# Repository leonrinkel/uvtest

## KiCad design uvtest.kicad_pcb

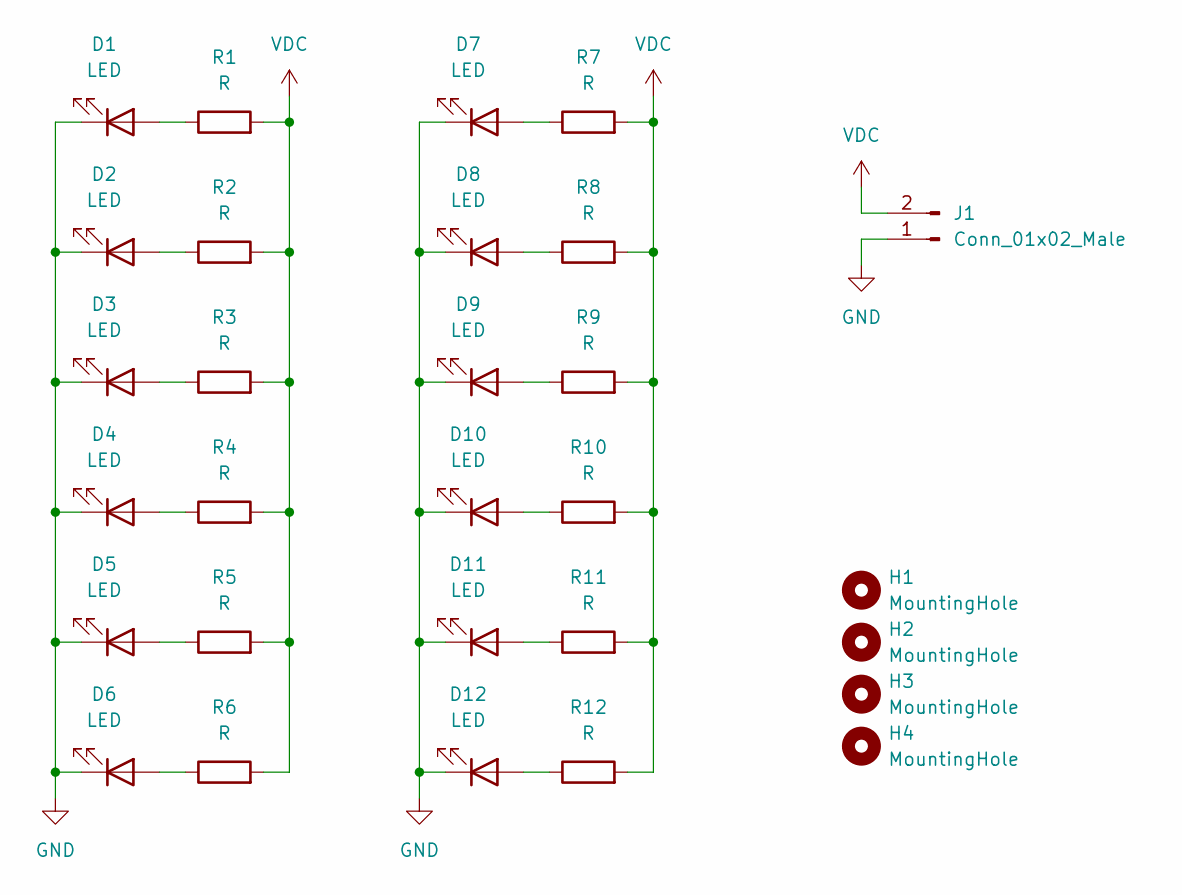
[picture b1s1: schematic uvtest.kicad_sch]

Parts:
D1: LED
D2, D3, D4, D5, D6, D7, D8, D9, D10, D11, D12: LED; LED_D5.0mm_Clear
H1: MountingHole
H2, H3, H4: MountingHole; MountingHole_2.7mm_M2.5
J1: Conn_01x02_Male
R1: R
R2, R3, R4, R5, R6, R7, R8, R9, R10, R11, R12: R; R_Axial_DIN0207_L6.3mm_D2.5mm_P10.16mm_Horizontal

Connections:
GND: D1.1 (K), D2.1 (K), D3.1 (K), D4.1 (K), D5.1 (K), D6.1 (K), D7.1 (K), D8.1 (K), D9.1 (K), D10.1 (K), D11.1 (K), D12.1 (K), J1.1
unnamed: D1.2 (A), R1.1
unnamed: D2.2 (A), R2.1
unnamed: D3.2 (A), R3.1
unnamed: D4.2 (A), R4.1
unnamed: D5.2 (A), R5.1
unnamed: D6.2 (A), R6.1
unnamed: D7.2 (A), R7.1
unnamed: D8.2 (A), R8.1
unnamed: D9.2 (A), R9.1
unnamed: D10.2 (A), R10.1
unnamed: D11.2 (A), R11.1
unnamed: D12.2 (A), R12.1
VDC: J1.2, R1.2, R2.2, R3.2, R4.2, R5.2, R6.2, R7.2, R8.2, R9.2, R10.2, R11.2, R12.2

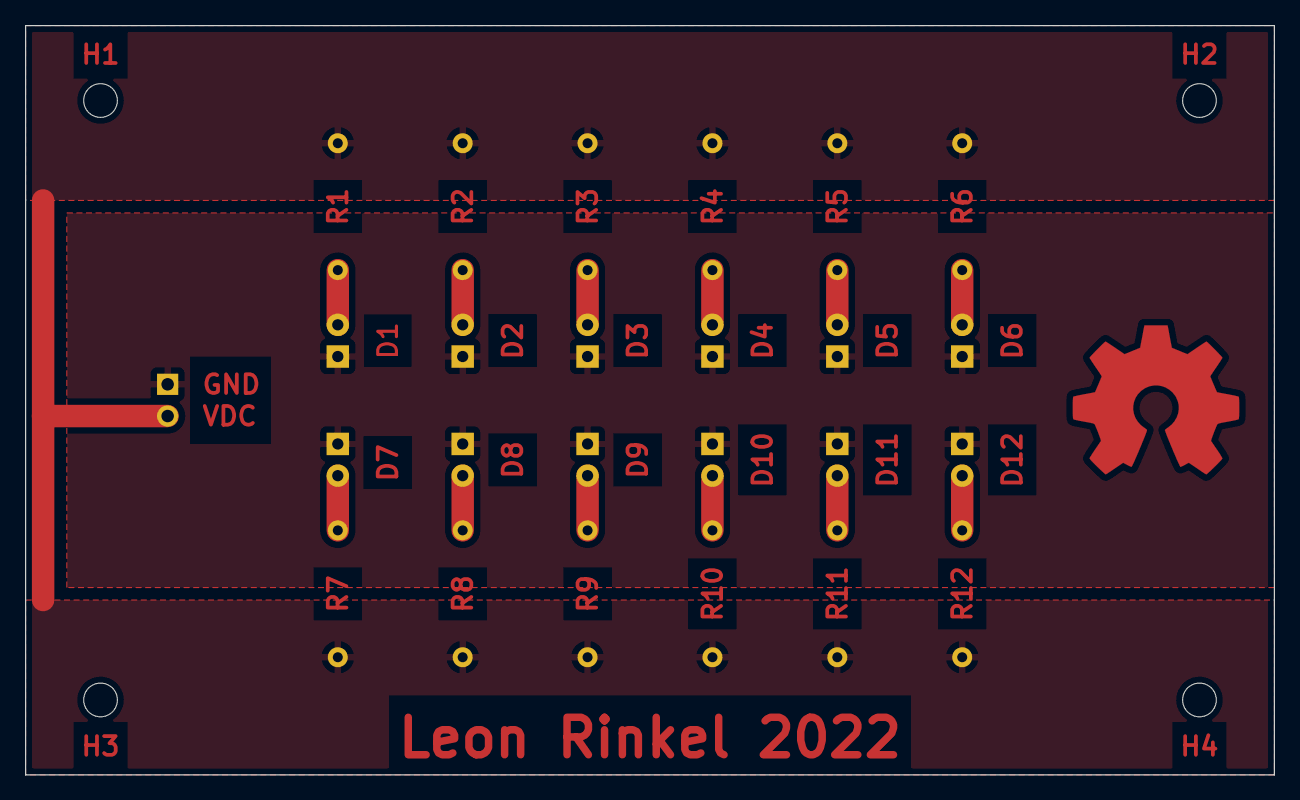
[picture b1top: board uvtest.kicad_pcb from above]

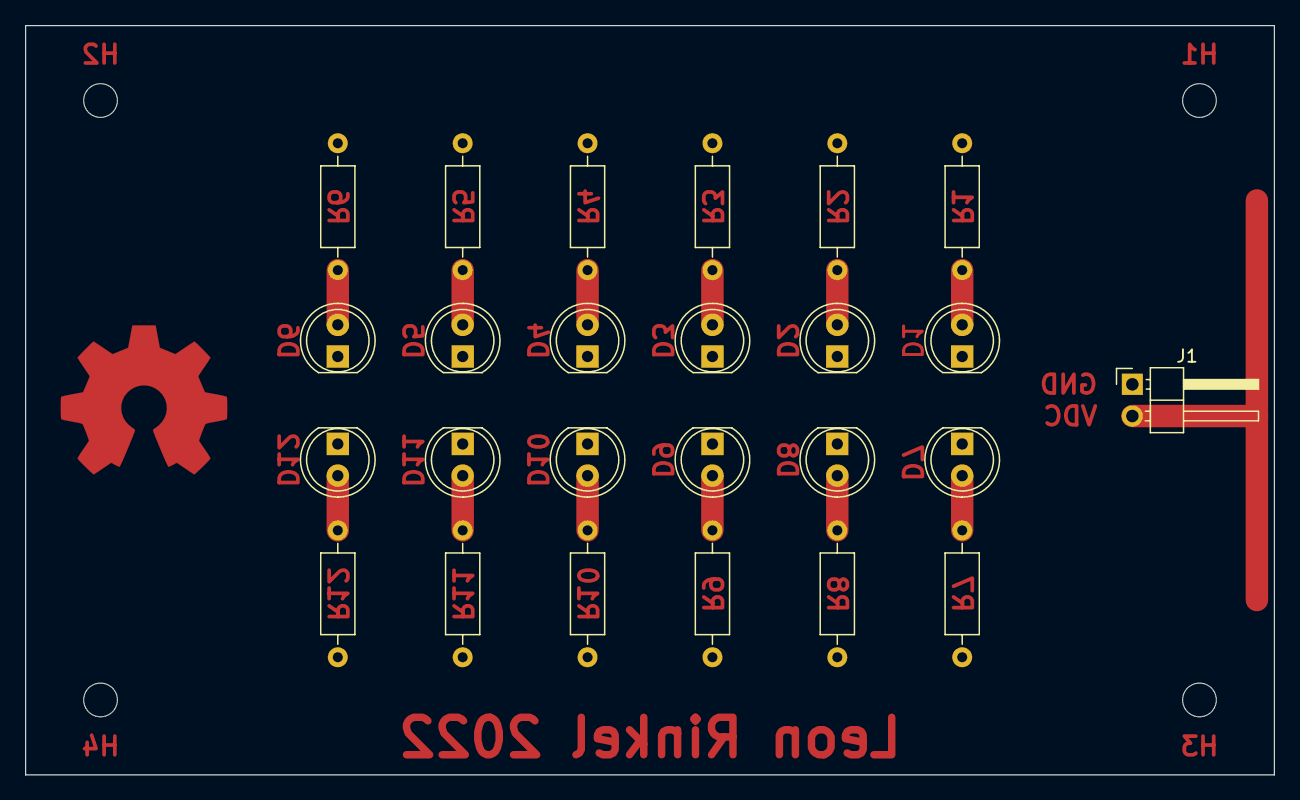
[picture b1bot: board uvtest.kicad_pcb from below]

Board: 2 copper layers, 100.0 x 60.0 mm, 29 parts (25 on the bottom side), 14 nets.
